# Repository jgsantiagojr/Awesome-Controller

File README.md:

### Jamie's Awesome Power Controller

Hi I'm Jamie! My Awesome Power Controller is a device that is controlled by a Teensy 4.1 and contains 2 H-Bridges, 4 MOSFET switches, and 4 Relays, as well as 4 General Purpose Input Outputs and a Touchscreen Display. Click on the image above for a demo!

The user can choose to either run a pre-written code option or control the different devices independently. An example of a pre-written code option is the Sensor Driven Motor. If the user selects this option, the controller will run a script that sets the PWM signal for H-Bridge 1 to the input from a sensor that is connected to GPIO 14. If the user chooses to control the devices independently then they will be able to individually toggle each of the relays, set the PWM values for each MOSFET switch and set the PWM values and direction for each H-Bridge. 

#### Suppliers

For my PCBs I used: JLCPCB

For my parts I used: Digikey, SparkFun and PJRC

#### Why this project?

This project was originally started for a class I took in the Fall of 2020, Microcontrollers for the Real World.  The point of this class was to be a remote, one-on-one session based class that would teach students to design and build a real-world controller using modular components. I decided that I wanted my project to be something that I could use for future projects and control high power systems with, so I decided to create this generic high power controller. 

#### The Process

##### The Start

The process for this project had a lot of ups and downs. I started off wanting to make everything from scratch and very poorly scoped expectations for what I could do in a semester. But after some initial designs and discussions as to why those designs wouldn't work or what could be better and cheaper, I ended up on a much cleaner path. 

My initial take on the project was that it could be board with a bunch of MOSFETs that the user could configure into different circuits (such as H-bridges and half-bridges) based on what they need to do. It was also supposed to be configurable from the users personal device via Bluetooth in addition to the on-board user interface. However, I quickly learned that this was unnecessarily complex and expensive, and way over-scoped for it to have a reasonable probability of success by the end of the semester. 

So I took a step back. Focused on other things for a day, and came back with a plan. I would use H-bridge modules and then simply have MOSFET switches available as well., in addition to my relay module and touchscreen display. 

##### Prototype 1

So a week or two after I pivoted to a more module-focused path, I had my first PCBs shipped. After soldering them together, I saw a few obvious problems:

- There was no way to tell if things were working with just the board, so I needed to add indicator LEDs so I could know if the device I was controlling was working without having to plug in a power source or motor/multimeter and so I could easily tell when the board was on. 
- There was no easy way to connect to ground. When I was trying to test that the right pins were outputting the right things there was no easy ground pin to base the measurements off of. So I needed to add a GND pin. 
- There were no GPIO pins. Had to add those. 
- No ON/OFF Switch, it was on whenever I plugged it in. I didn't like this because I wanted the device to be a tool I could keep on the table-top and that I should be able to turn it off without unplugging it. 

There were also a few problems that weren't so obvious:

- I2C line didn't have pull-up resistors. This made it so the teensy couldn't identify the relay board that I was trying to communicate with. 
- I2C line and the SPI lines shared the SCK pin. This was a big error, since SCK is the SPI clock. I discovered this was the problem after soldering a jumper cable between an SCL pin on the teensy and the clock pin on the I2C line and things started working. So I needed to make sure the I2C line was connected to SCL not SCK.

After I fixed all of these problems in the schematic and updated the layout I was able to send out for my second boards. 

##### Prototype 2

My second boards were also my final boards. At the same time as ordering them I began designing my mechanical packaging.  The boards worked fairly well but still have a few bugs:

- Something is wrong with the power. Every once in a while the LCD display just shows the backlighting and the only way to fix it is by restarting the entire device. 
- The layout of the board is very awkward. I need to re-lay all the components so that the board integrated more seamlessly with its packaging.
- Having a 6 pin connector for I2C is inconvient when only 4 pins are needed for i2c and the other 2 are for board power. I need to change that from a 6 pin to a 4 pin with a 2 port wire-to-board screw terminal. 

Something that wasn't really a bug but still a pain was the LEDs. They all worked, but since they were tiny and surface mount they took forever to solder on. If there is space to use LEDs that are easier to solder on I need to incorporate them. 

In terms of the mechanical packaging, my first attempt at a design was fun but didn't take into consideration that I would be 3D printing it, so I had to start from the beginning. For what would be my final package, I chose to have a simple plate and pegs to hold all of the modules secure next to each other in a clean way. 

I am proud to say that my second prototype works well and accomplishes what I wanted it to. I definitely learned a lot of circuit board design, mechanical packaging/3D printing and how to tie them in together.  

#### Parts List

| Part Name                               | Part Number           | Price per unit | Distributer |
| --------------------------------------- | --------------------- | -------------- | ----------- |
| 2 Pack BTS7940 High Power Driver Module | BTN7960               | 13.89          | Amazon      |
| 4 Pack of female 8pos cables            |                       | 8.75           | Amazon      |
| 4 Pin Molex Connector                   | 22232041              | .28            | Digikey     |
| 2 Position Wire to Board Terminal       | 796739-2              | 1.69           | Digikey     |
| 14 Pin Molex Connector                  | 22232141              | 1.56           | Digikey     |
| Power Jack Connector                    | PJ-202A               | .6             | Digikey     |
| .1uF Capacitor                          | C320C104K5R5TA7303    | .22            | Digikey     |
| 100uF Capacitor                         | JMK316ABJ107ML-T      | .56            | Digikey     |
| Level Converter 16DIP                   | CD40109BE             | .55            | Digikey     |
| 8 Position Headers for H-Bridge Module  | PPTC042LFBN-RC        | .15            | Digikey     |
| 24 Position Headers for Teensy          | PPTC241LFBN-RC        | 1.37           | Digikey     |
| 100 Ohm Resistor                        | CFR-25JB-52-100R      | .1             | Digikey     |
| 330 Ohm Resistor                        | CFR-25JB-52-330R      | .1             | Digikey     |
| 10K Ohm Resistor                        | CFR-25JB-52-10K       | .1             | Digikey     |
| 3v3 1A voltage regulator                | NCP1117DT33G          | .44            | Digikey     |
| 4 Pin Dual-Female Wire                  | 1597-1502-ND          | 3.38           | Digikey     |
| 2 Position Headers                      | S7000-ND              | .306           | Digikey     |
| LED BLUE CLEAR CHIP SMD                 | 160-1647-1-ND         | .262           | Digikey     |
| On-Off switch                           | 2449-RA1122DWR-ND     | .98            | Digikey     |
| DC Power Jack                           | 172-4207-ND           | 3.47           | Digikey     |
| LCD Touchscreen                         | DISPLAY_ILI9341_TOUCH | 15             | PJRC        |
| Teensy 4.1                              |                       | 26.95          | PJRC        |
| Qwiic Quad Relay                        | COM-16566             | 29.95          | SparkFun    |
| 60V N-Channel MOSFETs                   | FQP30N06L             | .95            | SparkFun    |

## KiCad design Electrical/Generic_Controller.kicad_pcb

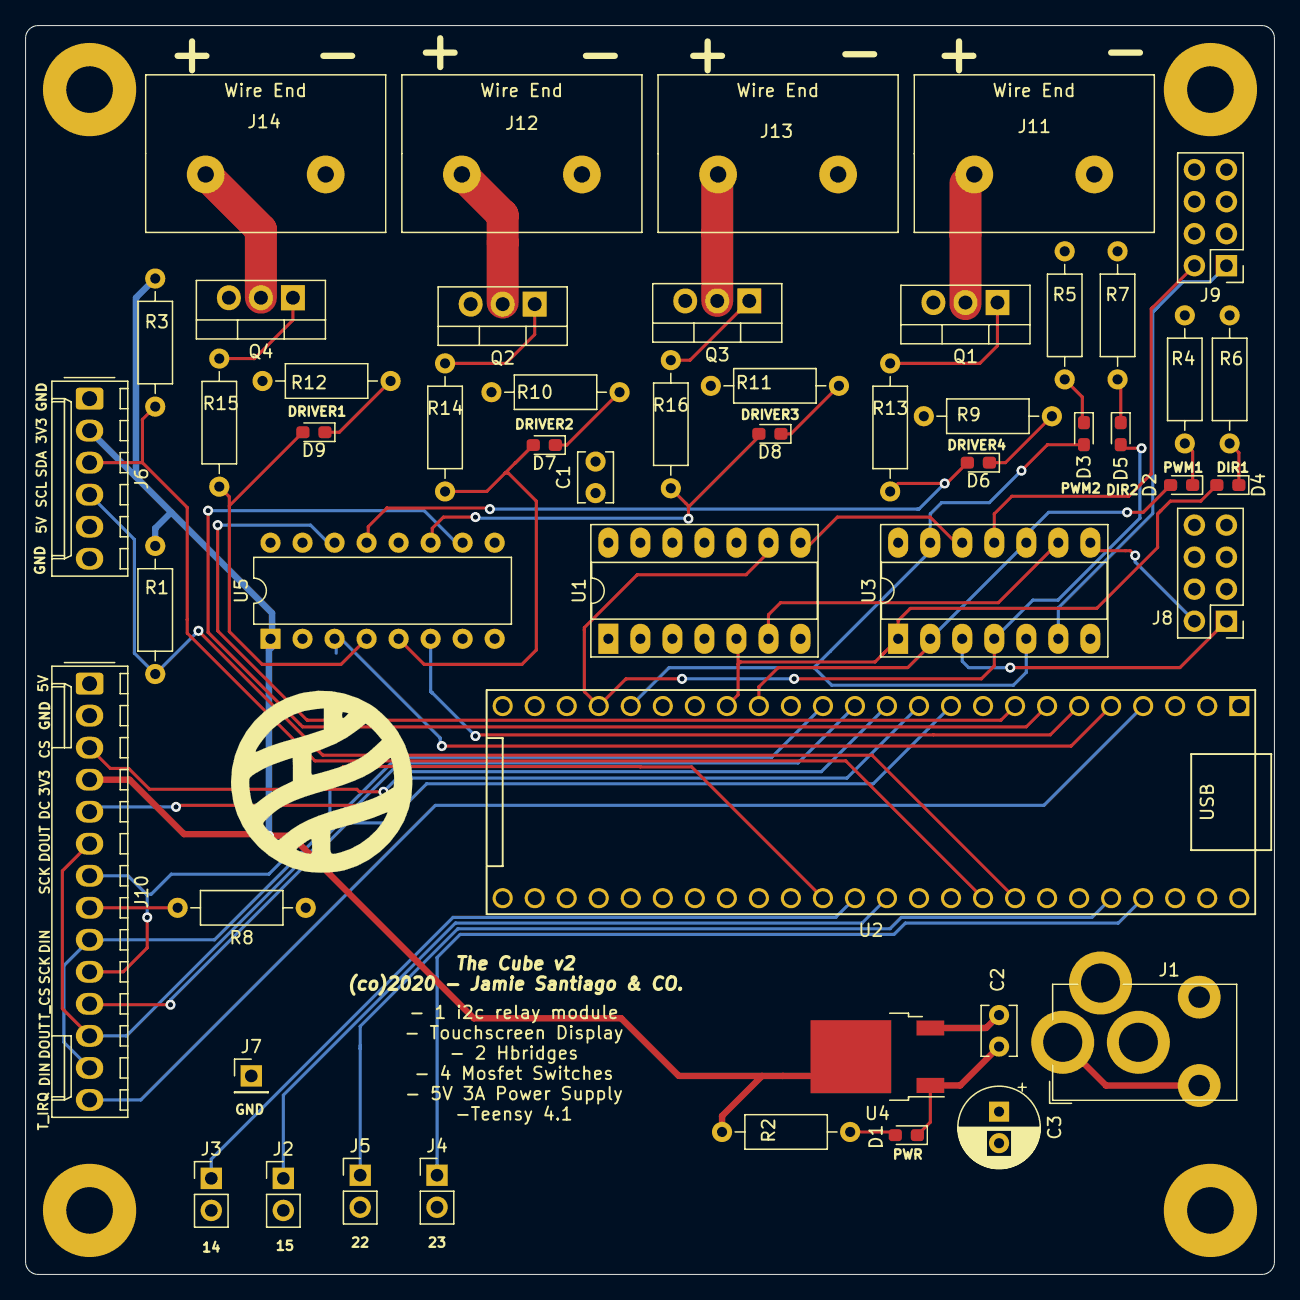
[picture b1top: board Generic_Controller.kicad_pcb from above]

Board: 4 copper layers, 99.1 x 99.1 mm, 52 parts (1 on the bottom side), 53 nets.

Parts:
C1, C2: .1uf; C_Disc_D3.8mm_W2.6mm_P2.50mm
C3: 100uF; CP_Radial_D6.3mm_P2.50mm
D1, D2, D3, D4, D5, D6, D7, D8, D9: LED; LED_0603_1608Metric_Pad1.05x0.95mm_HandSolder
J1: 5V from Wall; BarrelJack_Horizontal_3.1mmHole
J2: Pin 15; PinHeader_1x02_P2.54mm_Vertical
J3: Pin 14; PinHeader_1x02_P2.54mm_Vertical
J4: Pin 23; PinHeader_1x02_P2.54mm_Vertical
J5: Pin 22; PinHeader_1x02_P2.54mm_Vertical
J6: i2c; Molex_KK-254_AE-6410-06A_1x06_P2.54mm_Vertical
J7: GND_pin; PinHeader_1x01_P2.54mm_Vertical
J8: BTN7960B H-Bridge; PinHeader_2x04_P2.54mm_Vertical
J9: BTN7906B H-Bridge; PinHeader_2x04_P2.54mm_Vertical
J10: Display; Molex_KK-254_AE-6410-14A_1x14_P2.54mm_Vertical
J11: Driver4; 30A_WireToBoard_796739
J12: Driver2; 30A_WireToBoard_796739
J13: Driver3; 30A_WireToBoard_796739
J14: Driver1; 30A_WireToBoard_796739
Q1, Q2, Q3, Q4: FQP30N06L; TO-220-3_Vertical
R1, R3: 2.2K; R_Axial_DIN0207_L6.3mm_D2.5mm_P10.16mm_Horizontal
R2, R4, R5, R6, R7, R13, R14, R15, R16: 330; R_Axial_DIN0207_L6.3mm_D2.5mm_P10.16mm_Horizontal
R8: 100; R_Axial_DIN0207_L6.3mm_D2.5mm_P10.16mm_Horizontal
R9, R10, R11, R12: 10K; R_Axial_DIN0207_L6.3mm_D2.5mm_P10.16mm_Horizontal
SW1: SW_SPST; rockerSPST
U1: CD74HCT04E; DIP-14_W7.62mm_Socket_LongPads
U2: Teensy4.1; Teensy41
U3: CD74HCT08E; DIP-14_W7.62mm_Socket_LongPads
U4: NCP1117-3.3_TO252; TO-252-2
U5: CD40109BE; DIP-16_W7.62mm

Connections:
+3V3: J6.2, J10.4, R1.2, R2.1, R3.2, U4.2, U5.1
+5V: C1.1, C2.1, C3.1, J6.5, J8.3, J8.4, J8.7, J9.3, J9.4, J9.7, J10.1, R8.1, SW1.2, U1.14, U2.48, U3.14, U4.3, U5.2, U5.7, U5.9, U5.15, U5.16
/3V_driver_1: U2.5, U5.3
/3V_driver_2: U2.6, U5.6
/3V_driver_3: U2.7, U5.10
/3V_driver_4: U2.8, U5.14
/5V_driver_1: D9.2, R15.1, U5.4
/5V_driver_2: D7.2, R14.1, U5.5
/5V_driver_3: D8.2, R16.1, U5.11
/5V_driver_4: D6.2, R13.1, U5.13
/14: J3.1, U2.36
/15: J2.1, U2.37
/22: J5.1, U2.44
/23: J4.1, U2.45
/CS: J10.3, U2.12
/DC: J10.5, U2.11
/DIN: J10.9, J10.13, U2.14
/DIR1: D4.2, U1.5, U2.17, U3.1
/DIR2: D5.2, U1.9, U2.21, U3.4
/DOUT: J10.6, J10.12, U2.13
/LPWM1: J8.2, U3.8
/LPWM2: J9.2, U3.11
/PWM1: D2.2, U2.16, U3.2, U3.10
/PWM2: D3.2, U2.20, U3.5, U3.13
/RPWM1: J8.1, U3.3
/RPWM2: J9.1, U3.6
/SCK: J10.7, J10.10, U2.35
/SCL: J6.4, R1.1, U2.41
/SDA: J6.3, R3.1, U2.40
/T_CS: J10.11, U2.10
/T_IRQ: J10.14, U2.4
GND: C1.2, C2.2, C3.2, D1.1, J1.2, J2.2, J3.2, J4.2, J5.2, J6.1, J6.6, J7.1, J8.8, J9.8, J10.2, J11.2, J12.2, J13.2, J14.2, Q1.3, Q2.3, Q3.3, Q4.3, R4.2, R5.2, R6.2, R7.2, R9.1, R10.1, R11.1, R12.1, U1.7, U2.1, U2.34, U2.47, U3.7, U4.1, U5.8
unnamed: D1.2, R2.2
unnamed: D2.1, R4.1
unnamed: D3.1, R5.1
unnamed: D4.1, R6.1
unnamed: D5.1, R7.1
unnamed: D6.1, R9.2
unnamed: D7.1, R10.2
unnamed: D8.1, R11.2
unnamed: D9.1, R12.2
unnamed: J1.1, SW1.1
unnamed: J10.8, R8.2
unnamed: J11.1, Q1.2
unnamed: J12.1, Q2.2
unnamed: J13.1, Q3.2
unnamed: J14.1, Q4.2
unnamed: Q1.1, R13.2
unnamed: Q2.1, R14.2
unnamed: Q3.1, R16.2
unnamed: Q4.1, R15.2
unnamed: U1.6, U3.9
unnamed: U1.8, U3.12
